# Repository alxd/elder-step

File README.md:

# ElderStep

	By ALXD

## Components

- Thing1
- Thing2

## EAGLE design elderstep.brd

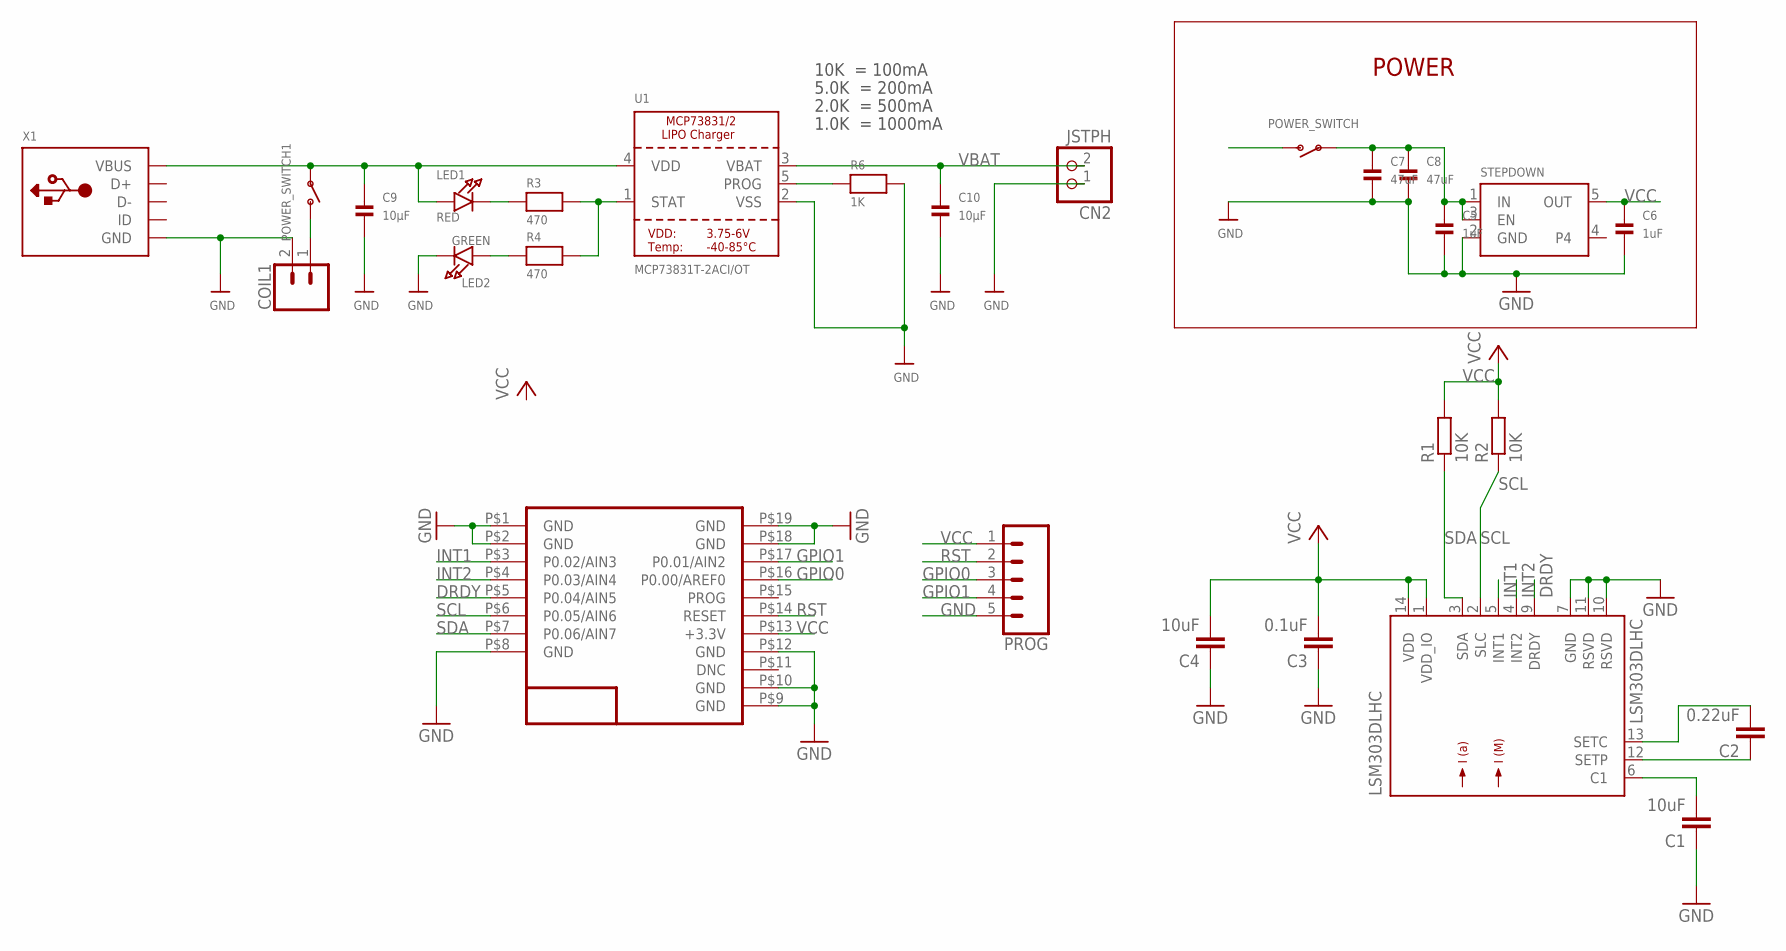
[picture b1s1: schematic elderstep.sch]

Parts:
C1, C4: 10uF; C0805
C2: 0.22uF; C0805
C3: 0.1uF; C0805
C5, C6: 1uF; 0603
C7, C8: 47uF; 0805
C9, C10: 10µF; 0805
CN2: JSTPH; JSTPH2
COIL1: CONN_02; 1X02
LED1: RED; CHIPLED_0805
LED2: GREEN; CHIPLED_0805
LSM303DLHC: LSM303DLHC; LGA-14
POWER_SWITCH, POWER_SWITCH1: SWITCH_SPST; SPST_SMT_19192
PROG: CONN_05; 1X05
R1, R2: 10K; R0805
R3, R4: 470; 0805
R6: 1K; 0805
RFD22301: RFD22301; RFD21733
STEPDOWN: VREG_SOT23-5; SOT23-5
U1: MCP73831T-2ACI/OT; SOT23-5
X1: USBMICRO_20329; 4UCONN_20329

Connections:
DRDY: LSM303DLHC.9 (DRDY), RFD22301.P$5 (P0.04/AIN5)
GND: C1.1, C3.1, C4.1, C5.2, C6.2, C7.2, C8.2, C9.2, C10.2, CN2.1, COIL1.2, LED2.C, LSM303DLHC.7 (GND), LSM303DLHC.10 (RSVD), LSM303DLHC.11 (RSVD), PROG.5, R6.2, RFD22301.P$1 (GND), RFD22301.P$2 (GND), RFD22301.P$8 (GND), RFD22301.P$9 (GND), RFD22301.P$10 (GND), RFD22301.P$12 (GND), RFD22301.P$18 (GND), RFD22301.P$19 (GND), STEPDOWN.2 (GND), U1.2 (VSS), X1.BASE@1 (GND), X1.BASE@2 (GND), X1.GND, X1.SPRT@1 (GND), X1.SPRT@2 (GND), X1.SPRT@3 (GND), X1.SPRT@4 (GND)
GPIO0: PROG.3, RFD22301.P$16 (P0.00/AREF0)
GPIO1: PROG.4, RFD22301.P$17 (P0.01/AIN2)
INT1: LSM303DLHC.5 (INT1), RFD22301.P$3 (P0.02/AIN3)
INT2: LSM303DLHC.4 (INT2), RFD22301.P$4 (P0.03/AIN4)
unnamed: LED1.C, R3.1
unnamed: R3.2, R4.2, U1.1 (STAT)
unnamed: C1.2, LSM303DLHC.6 (C1)
unnamed: C2.2, LSM303DLHC.13 (SETC)
unnamed: C2.1, LSM303DLHC.12 (SETP)
unnamed: R6.1, U1.5 (PROG)
unnamed: LED2.A, R4.1
unnamed: COIL1.1, POWER_SWITCH1.C (S)
RST: PROG.2, RFD22301.P$14 (RESET)
SCL: LSM303DLHC.2 (SLC), R2.1, RFD22301.P$6 (P0.05/AIN6)
SDA: LSM303DLHC.3 (SDA), R1.1, RFD22301.P$7 (P0.06/AIN7)
SWITCH_OUT: C5.1, C7.1, C8.1, POWER_SWITCH.B, STEPDOWN.1 (IN), STEPDOWN.3 (EN)
VBAT: C10.1, CN2.2, POWER_SWITCH.C (S), U1.3 (VBAT)
VCC: C3.2, C4.2, C6.1, LSM303DLHC.1 (VDD_IO), LSM303DLHC.14 (VDD), PROG.1, R1.2, R2.2, RFD22301.P$13 (+3.3V), STEPDOWN.5 (OUT)
VDD: C9.1, LED1.A, POWER_SWITCH1.B, U1.4 (VDD), X1.VBUS

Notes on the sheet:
POWER
10K = 100mA
5.0K = 200mA
2.0K = 500mA
1.0K = 1000mA

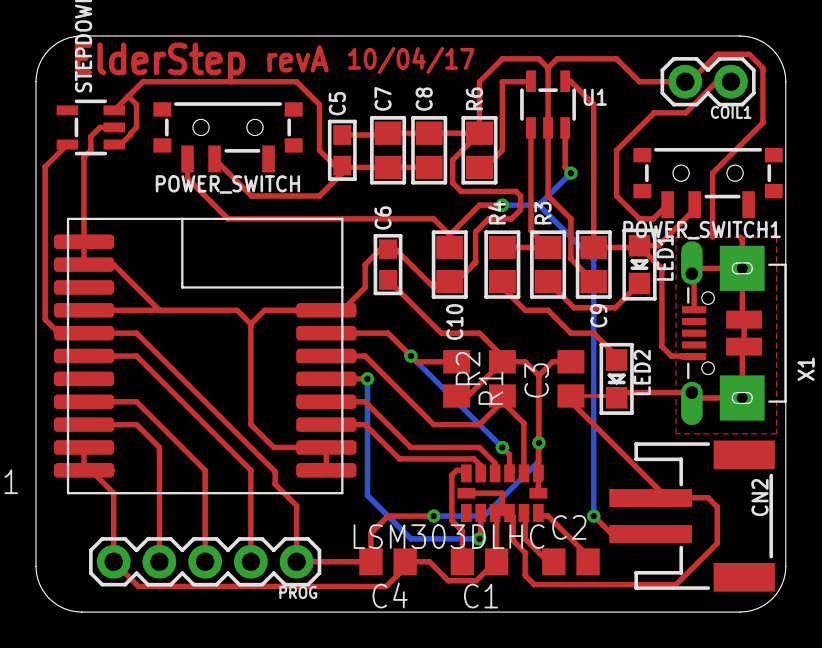
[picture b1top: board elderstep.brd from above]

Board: 2 copper layers, 41.7 x 32.0 mm, 27 parts (0 on the bottom side), 21 nets.

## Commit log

2017-10-04 readme
2017-10-05 revA

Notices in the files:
parts and their libraries:
microbuilder: This work is placed in the public domain, and may be freely used for commercial and non-commercial work with the following conditions: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
SparkFun-Connectors: Licensing: Creative Commons ShareAlike 4.0 International - https://creativecommons.org/licenses/by-sa/4.0
